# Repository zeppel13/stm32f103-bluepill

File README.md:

I designed a working simple STM32 devboard to learn how to use KiCad and design my own PCBs

MCU is a genuine STM32F103C8T6. I'll upload an STM32CubeIDE project soon, planning to also put an libopenCM3 project here. For the programming you'll need a standard ST-LINK programmer (A fake one might be working just fine). The PCB exposes a programming interface with SWD, CLK, +3V3 and GND and BOOT0 with Breakers. 

For the programming

    st-flash write firmware.bin 0x08000000 
    
works fine for me

### Goals of the Project
✅ **Learn to use KiCAD**  
✅ Complete all necessary steps to manufacture the board and proceed with prototypes  
✅ Create a Blue Pill-compatible board with a genuine STM32F103 (no clones like GD32, PY32, etc.)  
✅ Provide a base for future MCU PCB design  
✅ Ensure the PCB fits on a breadboard  
✅ Pay special attention to the routing of high-frequency signals: proper differential pairs for USB, a good ground plane, and always low-impedance return paths  
✅ Make it work  

---

### Non-Goals
- Using the newest or best features. STM32F103 might seem a bit outdated compared to newer STM32 offerings. A brand-name Micro USB-B connector will be used — no USB-C.  
- Power optimization (e.g., removing LEDs, using a more efficient voltage supply, or selecting a low-power MCU).  
- Price optimization. The plan is to build a small batch, not large quantities.  

---

### Errata
- The **BOOTP** header in the silkscreen should be **BOOT0**. I confused the technical jargon of Cortex boot modes with DHCP/BOOTP and didn’t realize the mistake until after producing the samples.  
- The SMD switch for BOOT0 was replaced with a pinout that can be configured with jumpers (HI/LOW).

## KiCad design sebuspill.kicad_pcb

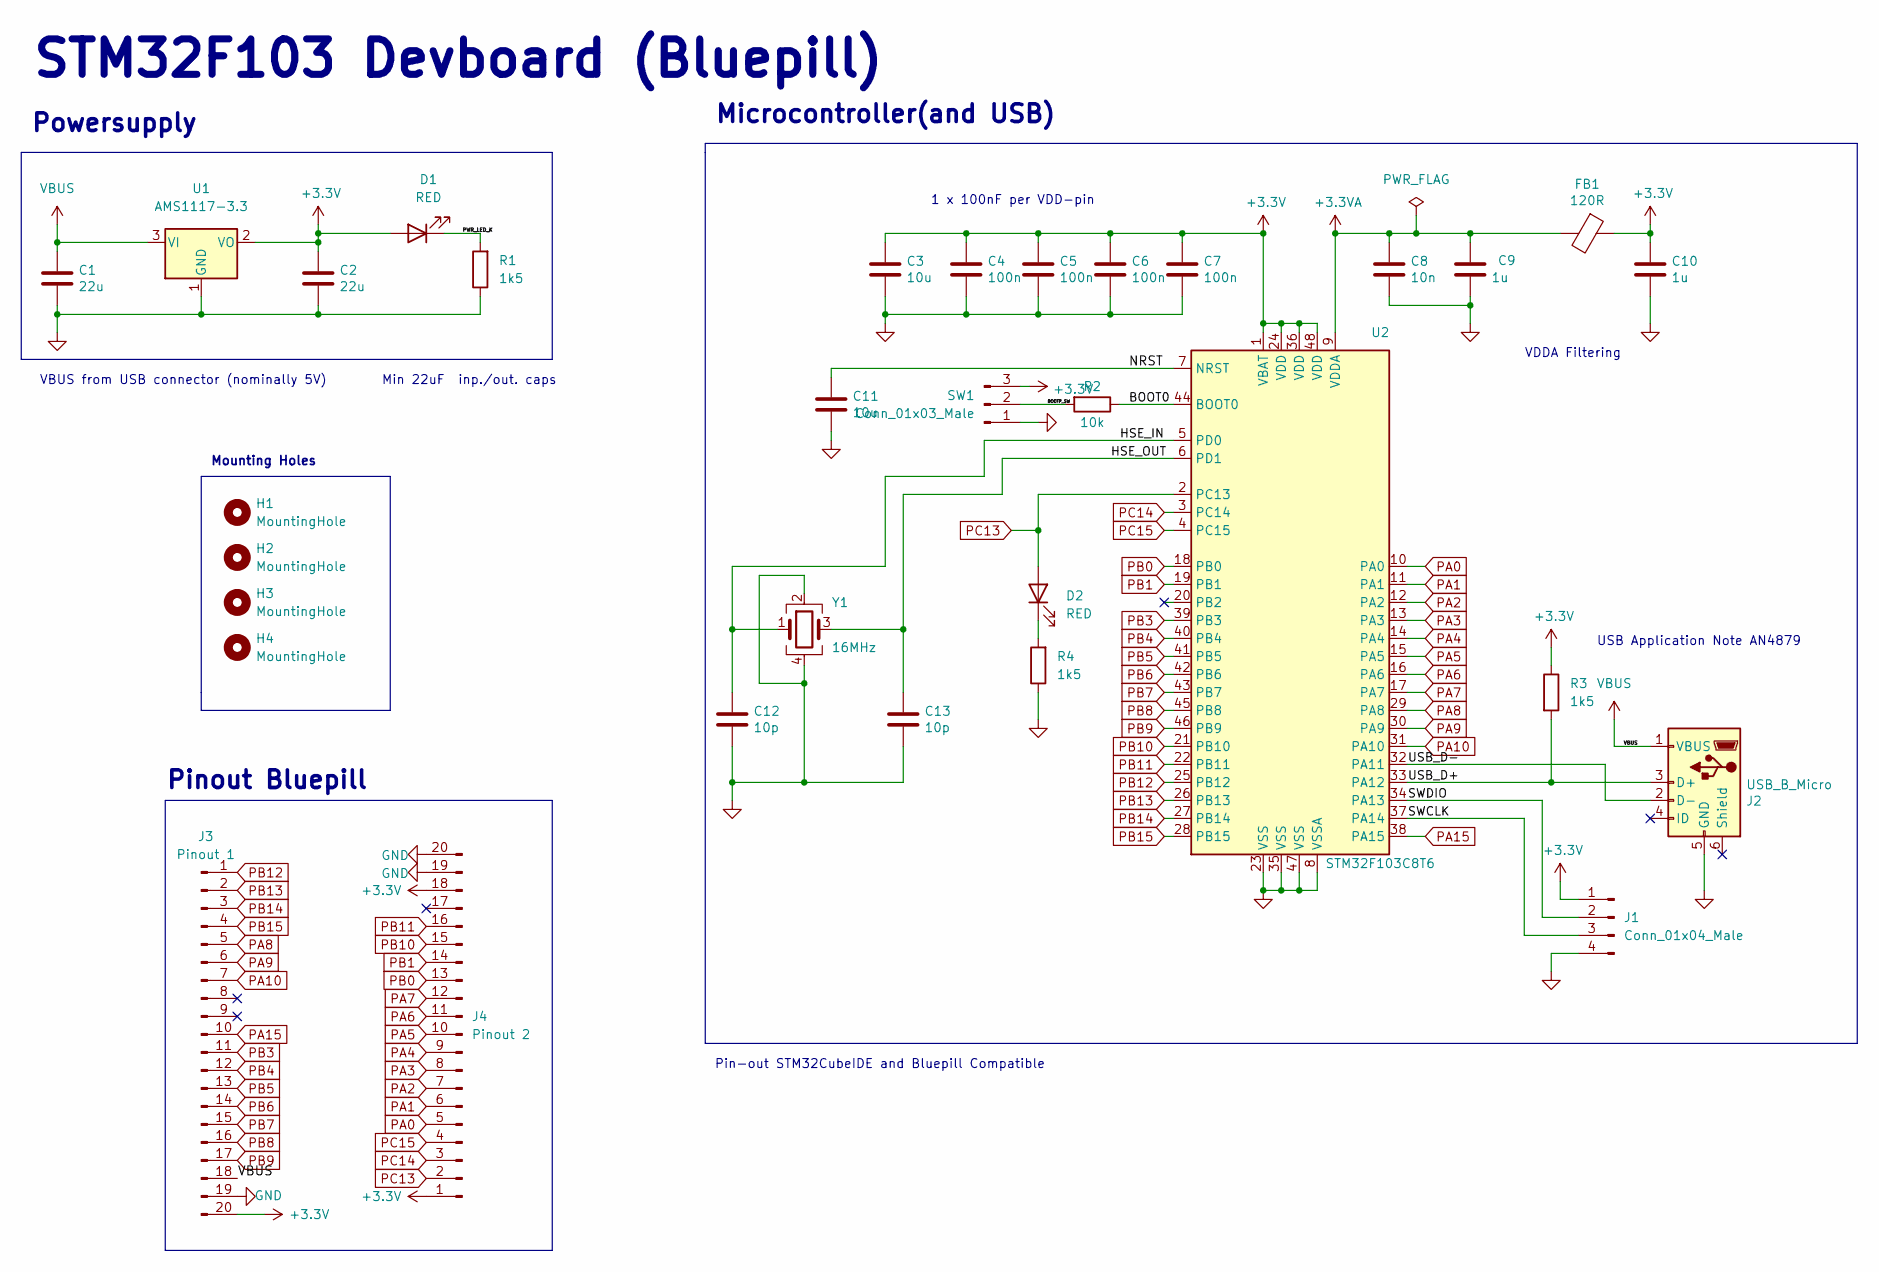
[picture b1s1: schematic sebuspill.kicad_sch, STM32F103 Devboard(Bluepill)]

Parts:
C1, C2: 22u; C_0805_2012Metric
C3, C11: 10u; C_0603_1608Metric
C4, C5, C6, C7: 100n; C_0402_1005Metric
C8: 10n; C_0402_1005Metric
C9, C10: 1u; C_0402_1005Metric
C12, C13: 10p; C_0402_1005Metric
D1, D2: RED; LED_0603_1608Metric
FB1: 120R; L_0603_1608Metric
H1, H2, H3, H4: MountingHole; MountingHole_2.2mm_M2
J1: Conn_01x04_Male; PinHeader_1x04_P2.54mm_Vertical
J2: USB_B_Micro; USB_Micro-B_Wuerth_629105150521
J3: Pinout 1; PinHeader_1x20_P2.54mm_Vertical
J4: Pinout 2; PinHeader_1x20_P2.54mm_Vertical
R1, R3, R4: 1k5; R_0402_1005Metric
R2: 10k; R_0402_1005Metric
SW1: Conn_01x03_Male
U1: AMS1117-3.3; SOT-223-3_TabPin2
U2: STM32F103C8T6; LQFP-48_7x7mm_P0.5mm
Y1: 16MHz; Crystal_SMD_3225-4Pin_3.2x2.5mm

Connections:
+3.3VA: C8.1, C9.1, FB1.2, U2.9 (VDDA)
+3V3: C2.1, C3.1, C4.1, C5.1, C6.1, C7.1, C10.1, D1.2 (A), FB1.1, J1.1, J3.20, J4.1, J4.18, R3.1, SW1.3, U1.2 (VO), U2.1 (VBAT), U2.24 (VDD), U2.36 (VDD), U2.48 (VDD)
/BOOT0: R2.1, U2.44 (BOOT0)
/BOOTP_SW: R2.2, SW1.2
/HSE_IN: C12.1, U2.5 (PD0), Y1.1
/HSE_OUT: C13.1, U2.6 (PD1), Y1.3
/NRST: C11.1, U2.7 (NRST)
/PWR_LED_K: D1.1 (K), R1.2
/SWCLK: J1.3, U2.37 (PA14)
/SWDIO: J1.2, U2.34 (PA13)
/USB_D+: J2.3 (D+), R3.2, U2.33 (PA12)
/USB_D-: J2.2 (D-), U2.32 (PA11)
GND: C1.2, C2.2, C3.2, C4.2, C5.2, C6.2, C7.2, C8.2, C9.2, C10.2, C11.2, C12.2, C13.2, J1.4, J2.5 (GND), J3.19, J4.19, J4.20, R1.1, R4.1, SW1.1, U1.1 (GND), U2.8 (VSSA), U2.23 (VSS), U2.35 (VSS), U2.47 (VSS), Y1.2, Y1.4
unnamed: D2.1 (K), R4.2
PA0: J4.5, U2.10 (PA0)
PA1: J4.6, U2.11 (PA1)
PA2: J4.7, U2.12 (PA2)
PA3: J4.8, U2.13 (PA3)
PA4: J4.9, U2.14 (PA4)
PA5: J4.10, U2.15 (PA5)
PA6: J4.11, U2.16 (PA6)
PA7: J4.12, U2.17 (PA7)
PA8: J3.5, U2.29 (PA8)
PA9: J3.6, U2.30 (PA9)
PA10: J3.7, U2.31 (PA10)
PA15: J3.10, U2.38 (PA15)
PB0: J4.13, U2.18 (PB0)
PB1: J4.14, U2.19 (PB1)
PB3: J3.11, U2.39 (PB3)
PB4: J3.12, U2.40 (PB4)
PB5: J3.13, U2.41 (PB5)
PB6: J3.14, U2.42 (PB6)
PB7: J3.15, U2.43 (PB7)
PB8: J3.16, U2.45 (PB8)
PB9: J3.17, U2.46 (PB9)
PB10: J4.15, U2.21 (PB10)
PB11: J4.16, U2.22 (PB11)
PB12: J3.1, U2.25 (PB12)
PB13: J3.2, U2.26 (PB13)
PB14: J3.3, U2.27 (PB14)
PB15: J3.4, U2.28 (PB15)
PC13: D2.2 (A), J4.2, U2.2 (PC13)
PC14: J4.3, U2.3 (PC14)
PC15: J4.4, U2.4 (PC15)
VBUS: C1.1, J2.1 (VBUS), J3.18, U1.3 (VI)

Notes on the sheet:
Min 22uF inp./out. caps
Powersupply
1 x 100nF per VDD-pin
Pinout Bluepill
Mounting Holes
USB Application Note AN4879
VBUS from USB connector (nominally 5V)
Microcontroller(and USB)
Pin-out STM32CubeIDE and Bluepill Compatible
STM32F103 Devboard (Bluepill)
VDDA Filtering

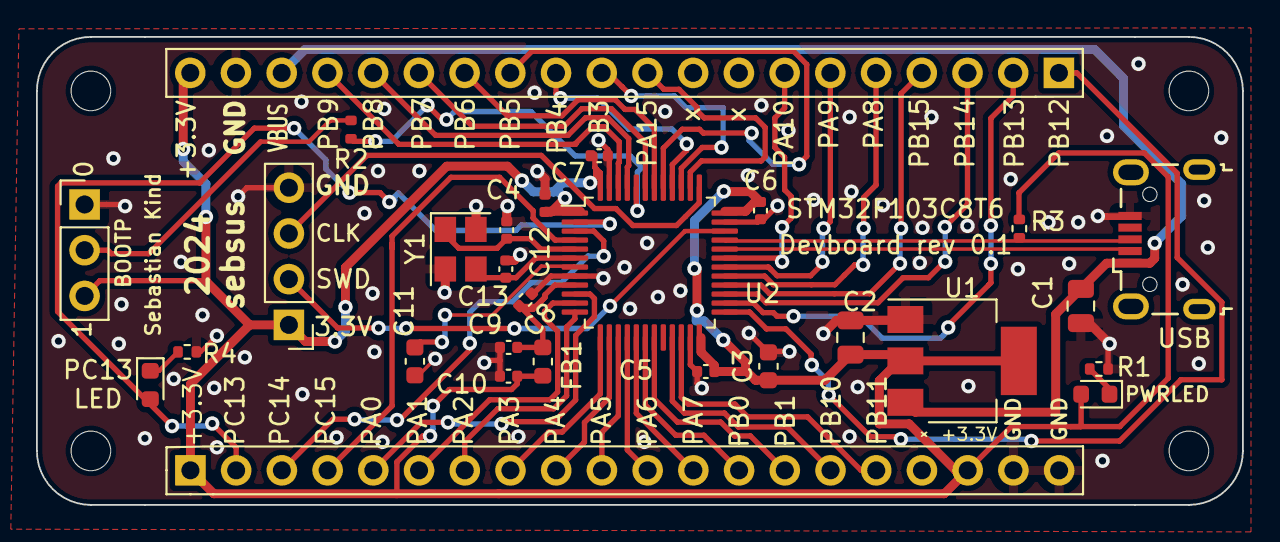
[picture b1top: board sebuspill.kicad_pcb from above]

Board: 2 copper layers, 67.0 x 26.0 mm, 32 parts (0 on the bottom side), 45 nets.

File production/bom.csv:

Designator,Footprint,Quantity,Value,LCSC Part #
"C1, C2",0805,2,22u,
"C10, C9",0402,2,1u,
"C11, C3",0603,2,10u,
"C12, C13",0402,2,10p,
"C4, C5, C6, C7",0402,4,100n,
C8,0402,1,10n,
"D1, D2",0603,2,RED,
FB1,0603,1,120R,
"H1, H2, H3, H4",MountingHole_2.2mm_M2,4,MountingHole,
J1,PinHeader_1x04_P2.54mm_Vertical,1,Conn_01x04_Male,
J2,USB_Micro-B_Wuerth_629105150521,1,USB_B_Micro,
J3,PinHeader_1x20_P2.54mm_Vertical,1,Pinout 1,
J4,PinHeader_1x20_P2.54mm_Vertical,1,Pinout 2,
"R1, R3, R4",0402,3,1k5,
R2,0402,1,10k,
SW1,PinHeader_1x03_P2.54mm_Vertical,1,Conn_01x03_Male,
U1,SOT-223-3_TabPin2,1,AMS1117-3.3,
U2,LQFP-48_7x7mm_P0.5mm,1,STM32F103C8T6,
Y1,Crystal_SMD_3225-4Pin_3.2x2.5mm,1,16MHz,

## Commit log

2024-09-16 inital commit of bluepill board
2024-09-17 added all components, next step routing and outline
2024-09-18 set pinheaders to fit on a bread board
2024-09-18 routing halfly done
2024-09-18 still routing
2024-09-18 trying to route groundplane between all backside wires
2024-09-18 finished i think
2024-09-18 Update README.md
    added images
2024-09-19 changed SMD switch to Jumper bc JLCPCB hat no in stock and added User programmable LED to PC13
2024-09-19 took Jacopops Feedback <3 and rerouted some traces
2024-09-19 ordered at JLCPCP
2025-01-19 added errata
2025-01-21 Added image of the produced prototype
